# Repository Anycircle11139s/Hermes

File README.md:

This is my Hermes Project:
Ngl, I created my hermes project cause I was bored and thought it would be a good idea, also, when I started it was a tier 2 project and said it would only take 5 hours... Later it would change to tier 1 with 10 hours :(

I mostly enjoyed the project, it helped me learn about resistors and datasheets, also it wasn't to complex. I'm also glad we don't have to CAD a case, because that would just be annoying.

The schematic took me a while because I had to find the footprint and symbol for my chosen sensor (temp and humidity sensor). I also had to learn about how to use my resistors from people in slack. It was an educational experience.

The PCB was fairly easy for me, because I'm used to more complex projects such as hackpads and split keyboards (which require a lot more routing and pain), so the Hermes project was a nice break. Once I finished the PCB, I added the silkscreen layer. 

I spent the most time on the BOM because getting all the parts under $25 USD was difficult, but I eventually managed it. I originally started with 3 different companies (LCSC, JLCPCB and Ali-express), this wouldnt work because of the 3 seperate shipping cost, 2 hours later, I finally got it to under $25 USD even tho I still had 3 different companies, which included digikey, ali-express and JLCPCB, JLCPCB was 5.50 total, I got the oled and rotary encoder from ali express because of cheap prices and free shipping, I got the rest of the parts from digikey because they had the cheapest parts even though digikey had a 6.99 USD shipping fee along with two dollars in tariffs/tax.

|Name                     |Purpose                                              |Quantity|Total Cost (USD)|Link                                                                                                                                                                                     |Distributor|
|-------------------------|-----------------------------------------------------|--------|----------------|-----------------------------------------------------------------------------------------------------------------------------------------------------------------------------------------|-----------|
|Oled                     |screen                                               |1       |2.30            |https://www.aliexpress.com/item/1005006636072295.html?mp=1&pdp_npi=6@dis!USD!USD%203.47!USD%200.99!!USD%200.99!!!@2102f22c17753786454871604ea4a4!12000037978554141!ct!AU!7402515296!!1!0!|ali=express|
|resistor                 |for ressisting                                       |36      |0.98            |https://www.digikey.com/en/products/detail/stackpole-electronics-inc/CF12JT4K70/1741152                                                                                                  |Digikey    |
|Rp2040                   |motherboard                                          |1       |3.49            |https://www.digikey.com/en/products/detail/seeed-technology-co-ltd/100045204/28959890                                                                                                    |Digikey    |
|Ec11 rotary encoder      |so i can change brightness of oled to prevent burn in|1       |1.47            |https://www.aliexpress.com/item/1005006693443387.html?mp=1&pdp_npi=6@dis!USD!USD%201.47!USD%200.99!!USD%200.99!!!@210328df17757913589444878e58cd!12000048311239365!ct!AU!7513952212!!1!0!|ali express|
|LM75AD,118               |Temperature sensor                                   |1       |0.71            |https://www.digikey.com/en/products/detail/nxp-usa-inc/LM75ADP-118/1156588                                                                                                               |Digikey    |
|PCB creating and shipping|For pcb                                              |1       |5.50            |                                                                                                                                                                                         |JLCPCB     |

Building the thing:
Once I recieved all the parts, I started soldering, I tried normally soldering the LM75AD sensor without flux, but the pads kept bridging, so I applied flux. Since I didn't/don't have a solder wick, it was slightly harder, but I seperated all the bridges by flicking the soldering iron in a way that broke the bridges. Once the sensor was soldered on, I moved on to the rotary encoder, it was pretty simple, but my soldering was pretty bad on it. Then, I moved on to the oled, with only 4 pins, it was really easy, I just had to make sure it was in the correct position before I soldered it. Next, I soldered the headers to the rp2040 and soldered it onto the PCB. This was my favourite part because I find it extremely satisfying to solder the pins on microcontrollers. Lastly, I soldered on the resistors. The resistors were kind of weird, because the hole distance is a lot smaller than the actual resistors, so I had to squeeze them in. Once I had finished soldering, I moved on to the code. I got my intitial code, uploaded it, uploaded the drivers or whatever its called and ran the code from thonny. Originally it didn't work becayse the oled screen was set to 64 as the y axis height instead of 32. Then I had to do some random other trouble shooting because the screen was upside down and some other stuff, but after a while, it finally worked.

https://github.com/user-attachments/assets/9b167287-3994-496b-82d9-43ea8c0a6dbe

https://github.com/user-attachments/assets/fa248c13-c449-4ee9-a2be-12438f792acb

https://github.com/user-attachments/assets/527572af-bf87-4742-be0e-cb3ad4938c7c

https://github.com/user-attachments/assets/440db2dd-6235-4dd3-aeeb-82b491f24ae7

https://github.com/user-attachments/assets/d056f70a-cc38-4e82-8550-2bf955608510

https://github.com/user-attachments/assets/0cdc1f9a-8a88-437c-a1f9-4a4462cc4919

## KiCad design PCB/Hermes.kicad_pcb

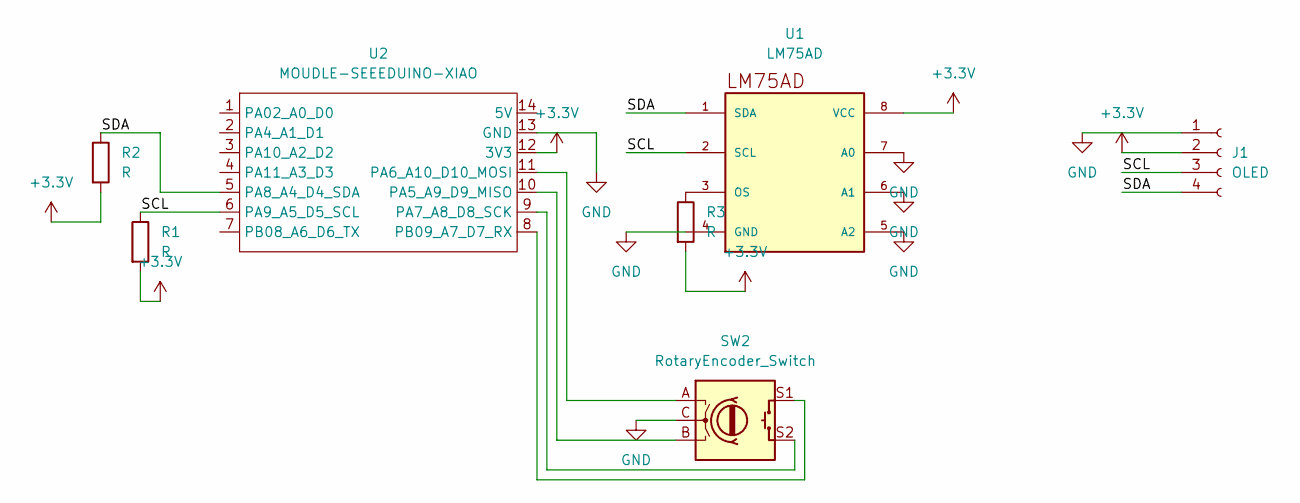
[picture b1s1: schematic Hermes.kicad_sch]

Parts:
J1: OLED; SSD1306 OLED 128x32
R1, R2, R3: R; RESAD1100W55L680D260
SW2: RotaryEncoder_Switch; RotaryEncoder_Alps_EC11E-Switch_Vertical_H20mm
U1: LM75AD; SOIC-8
U2: MOUDLE-SEEEDUINO-XIAO; XIAO-Generic-Hybrid-14P-2.54-21X17.8MM

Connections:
+3.3V: J1.2, R1.2, R2.2, R3.2, U1.8 (VCC), U2.12 (3V3)
/SCL: J1.3, R1.1, U1.2 (SCL), U2.6 (PA9_A5_D5_SCL)
/SDA: J1.4, R2.1, U1.1 (SDA), U2.5 (PA8_A4_D4_SDA)
GND: J1.1, SW2.C, U1.4 (GND), U1.5 (A2), U1.6 (A1), U1.7 (A0), U2.13 (GND)
unnamed: R3.1, U1.3 (OS)
unnamed: SW2.B, U2.10 (PA5_A9_D9_MISO)
unnamed: SW2.A, U2.11 (PA6_A10_D10_MOSI)
unnamed: SW2.S2, U2.9 (PA7_A8_D8_SCK)
unnamed: SW2.S1, U2.8 (PB09_A7_D7_RX)

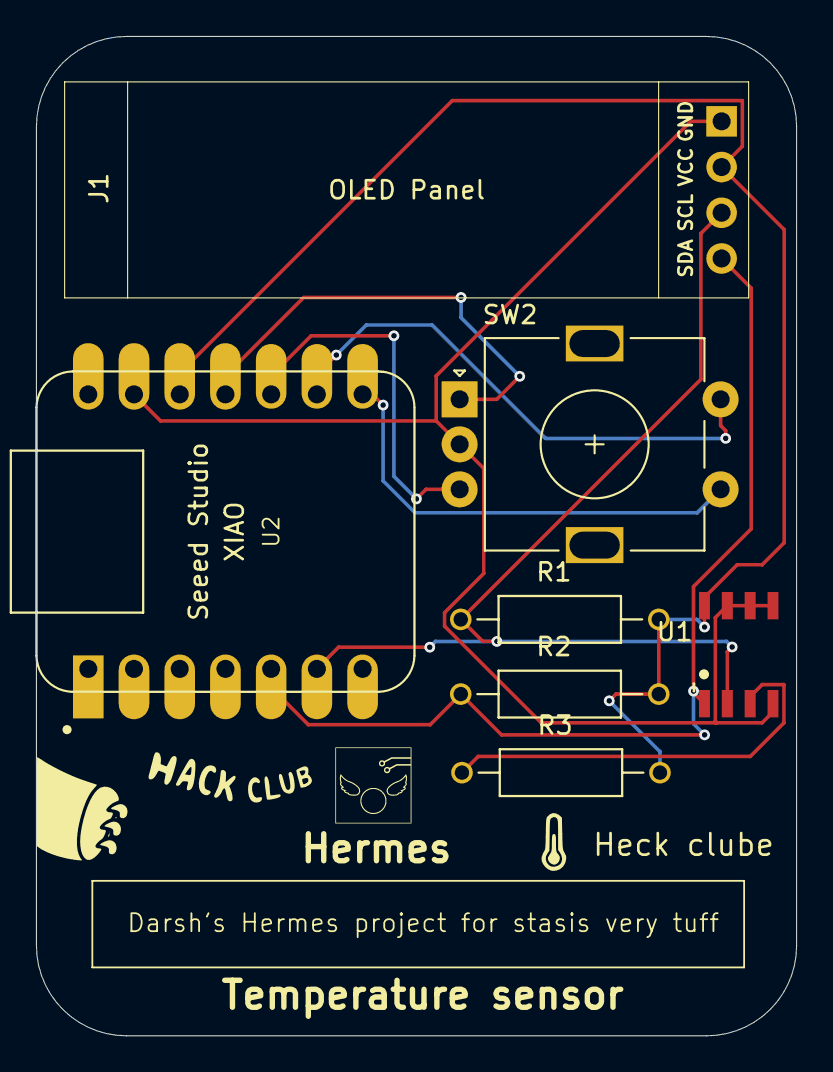
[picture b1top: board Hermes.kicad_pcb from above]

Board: 2 copper layers, 42.2 x 55.5 mm, 10 parts (0 on the bottom side), 9 nets.

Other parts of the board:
Heck clube: LOGO
Hermes: LOGO
Temperature sensor: LOGO

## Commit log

2026-03-25 Create idk
2026-04-06 Update README.md with component details
    Added a table listing components, their purposes, quantities, costs, links, and distributors.
